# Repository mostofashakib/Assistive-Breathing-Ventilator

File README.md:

# Assistive-Breathing-Ventilator

This is an implementation of a mechanical ventilator using bicycle pumps, a rack & pinion system attached to a pressure sensor, and an airflow sensor. The ventilator is controlled by an Arduino Mega board and is coded in C++ to make a low-cost DIY Ventilator.

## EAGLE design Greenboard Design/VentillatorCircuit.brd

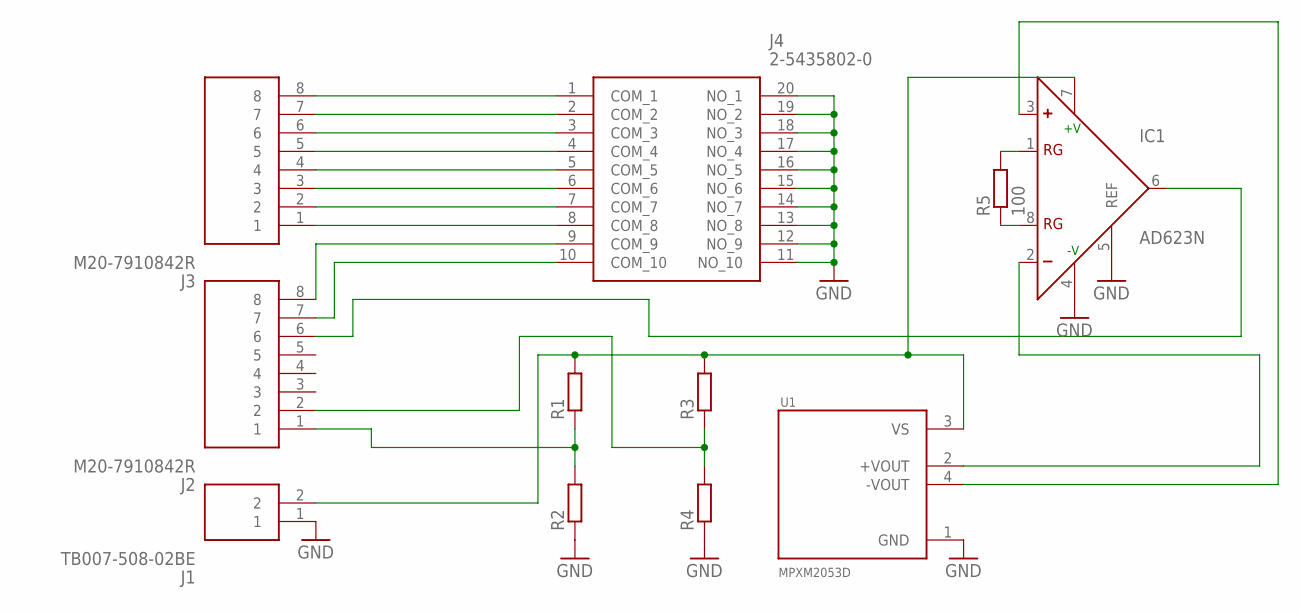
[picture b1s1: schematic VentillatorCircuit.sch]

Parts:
IC1: AD623N; DIL08
J1: TB007-508-02BE; TB00750802BE
J2, J3: M20-7910842R; M207910842R
J4: 2-5435802-0; 254358020
R1, R2, R3, R4: R-EU_0207/12; 0207/12
R5: 100; 0207/12
U1: MPXM2053D; SOT127P1219X419-5N

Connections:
GND: IC1.4 (-V), IC1.5 (REF), J1.1, J4.11 (NO_10), J4.12 (NO_9), J4.13 (NO_8), J4.14 (NO_7), J4.15 (NO_6), J4.16 (NO_5), J4.17 (NO_4), J4.18 (NO_3), J4.19 (NO_2), J4.20 (NO_1), R2.1, R4.1, U1.1 (GND)
unnamed: J3.8, J4.1 (COM_1)
unnamed: J3.7, J4.2 (COM_2)
unnamed: J3.6, J4.3 (COM_3)
unnamed: J3.5, J4.4 (COM_4)
unnamed: J3.4, J4.5 (COM_5)
unnamed: J3.3, J4.6 (COM_6)
unnamed: J3.2, J4.7 (COM_7)
unnamed: J3.1, J4.8 (COM_8)
unnamed: J2.8, J4.9 (COM_9)
unnamed: J2.7, J4.10 (COM_10)
unnamed: J2.1, R1.1, R2.2
unnamed: J2.2, R3.1, R4.2
unnamed: IC1.1 (RG), R5.2
unnamed: IC1.8 (RG), R5.1
unnamed: IC1.3 (+), U1.4 (-VOUT)
unnamed: IC1.2 (-), U1.2 (+VOUT)
unnamed: IC1.7 (+V), J1.2, R1.2, R3.2, U1.3 (VS)
unnamed: IC1.6 (OUT), J2.6

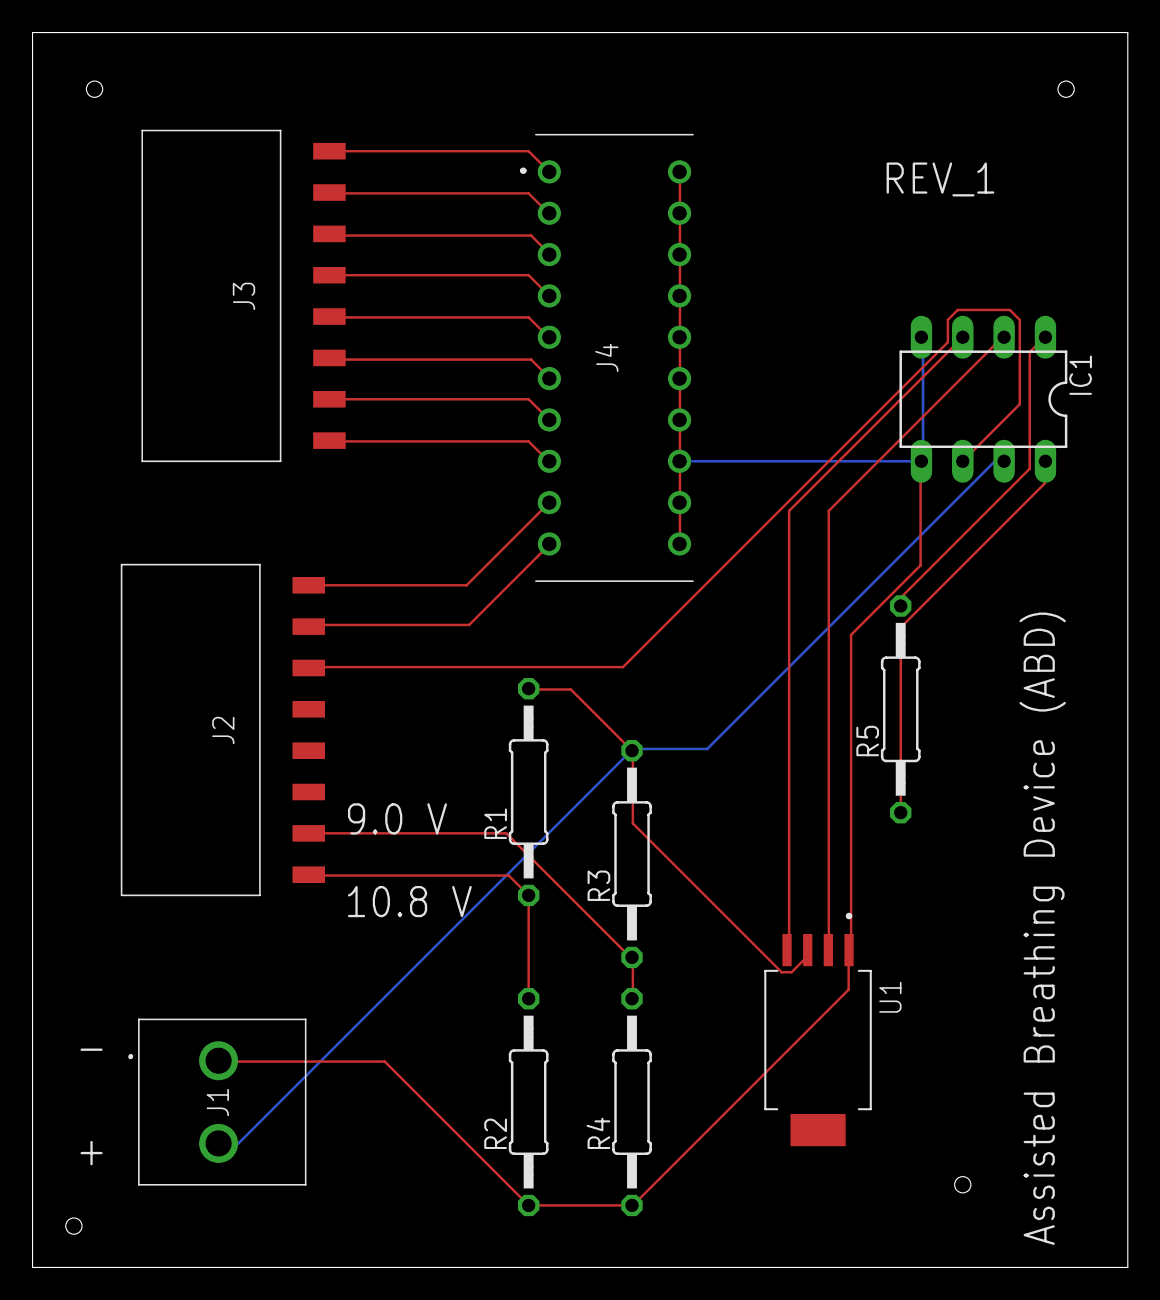
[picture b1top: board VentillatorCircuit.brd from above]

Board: 2 copper layers, 67.3 x 75.9 mm, 11 parts (0 on the bottom side), 19 nets.

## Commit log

2020-05-23 complete project
